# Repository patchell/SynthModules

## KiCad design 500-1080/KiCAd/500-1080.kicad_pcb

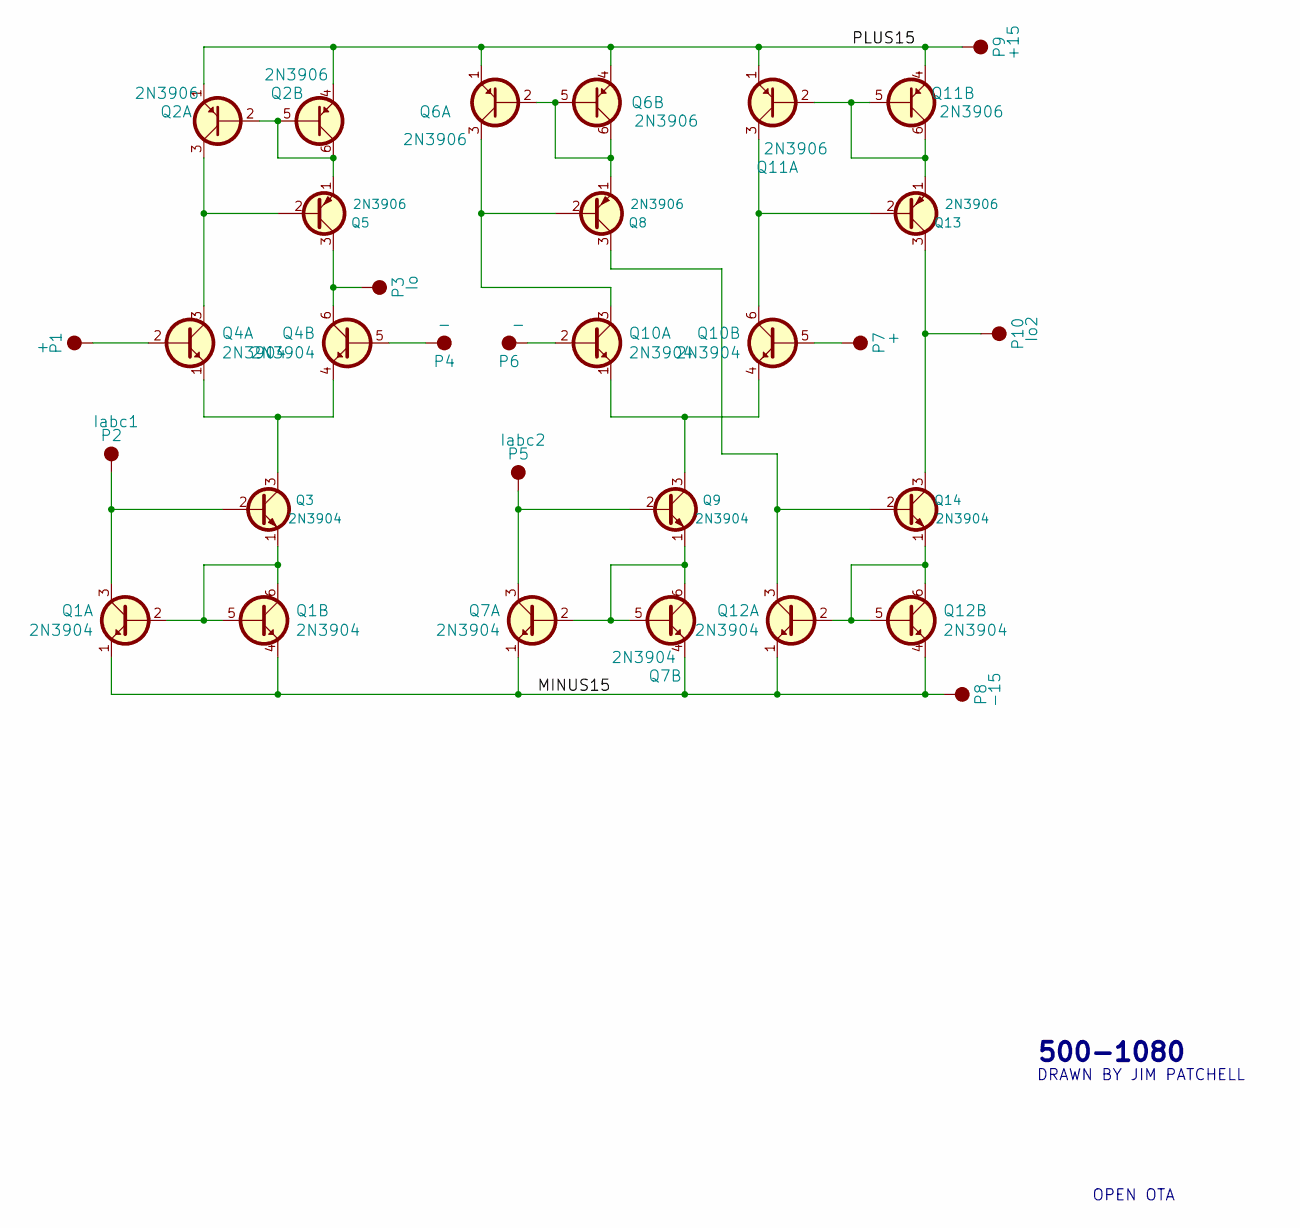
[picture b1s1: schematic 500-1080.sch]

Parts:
P1, P7: +; PAD
P2: Iabc1; PAD
P3: Io; PAD
P4, P6: -; PAD
P5: Iabc2; PAD
P8: -15; PAD
P9: +15; PAD
P10: Io2; PAD
Q1, Q4, Q7, Q10, Q12: 2N3904; DUAL_TO92
Q2, Q6, Q11: 2N3906; DUAL_TO92
Q3, Q9, Q14: 2N3904; TO92
Q5, Q8, Q13: 2N3906; TO92

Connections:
/MINUS15: P8.1, Q1.1 (EMITTER), Q1.4 (EMITTER), Q7.1 (EMITTER), Q7.4 (EMITTER), Q12.1 (EMITTER), Q12.4 (EMITTER)
/PLUS15: P9.1, Q2.1 (Emitter), Q2.4 (Emitter), Q6.1 (Emitter), Q6.4 (Emitter), Q11.1 (Emitter), Q11.4 (Emitter)
unnamed: P1.1, Q4.2 (Base)
unnamed: P2.1, Q1.3 (Collector), Q3.2 (B)
unnamed: P3.1, Q4.6 (Collector), Q5.3 (C)
unnamed: P4.1, Q4.5 (Base)
unnamed: P5.1, Q7.3 (Collector), Q9.2 (B)
unnamed: P6.1, Q10.2 (Base)
unnamed: P7.1, Q10.5 (Base)
unnamed: P10.1, Q13.3 (C), Q14.3 (C)
unnamed: Q1.2 (Base), Q1.5 (Base), Q1.6 (Collector), Q3.1 (E)
unnamed: Q2.2 (Base), Q2.5 (Base), Q2.6 (Collector), Q5.1 (E)
unnamed: Q2.3 (Collector), Q4.3 (Collector), Q5.2 (B)
unnamed: Q3.3 (C), Q4.1 (EMITTER), Q4.4 (EMITTER)
unnamed: Q6.2 (Base), Q6.5 (Base), Q6.6 (Collector), Q8.1 (E)
unnamed: Q7.2 (Base), Q7.5 (Base), Q7.6 (Collector), Q9.1 (E)
unnamed: Q9.3 (C), Q10.1 (EMITTER), Q10.4 (EMITTER)
unnamed: Q6.3 (Collector), Q8.2 (B), Q10.3 (Collector)
unnamed: Q10.6 (Collector), Q11.3 (Collector), Q13.2 (B)
unnamed: Q11.2 (Base), Q11.5 (Base), Q11.6 (Collector), Q13.1 (E)
unnamed: Q12.2 (Base), Q12.5 (Base), Q12.6 (Collector), Q14.1 (E)
unnamed: Q8.3 (C), Q12.3 (Collector), Q14.2 (B)

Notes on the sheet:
OPEN OTA
500-1080
DRAWN BY JIM PATCHELL

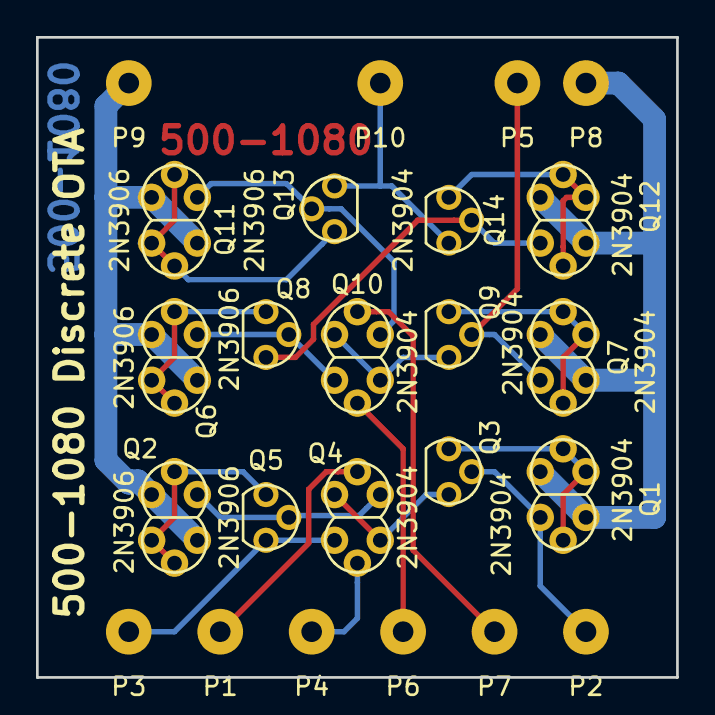
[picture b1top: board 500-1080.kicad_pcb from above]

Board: 2 copper layers, 35.6 x 35.6 mm, 24 parts (0 on the bottom side), 22 nets.

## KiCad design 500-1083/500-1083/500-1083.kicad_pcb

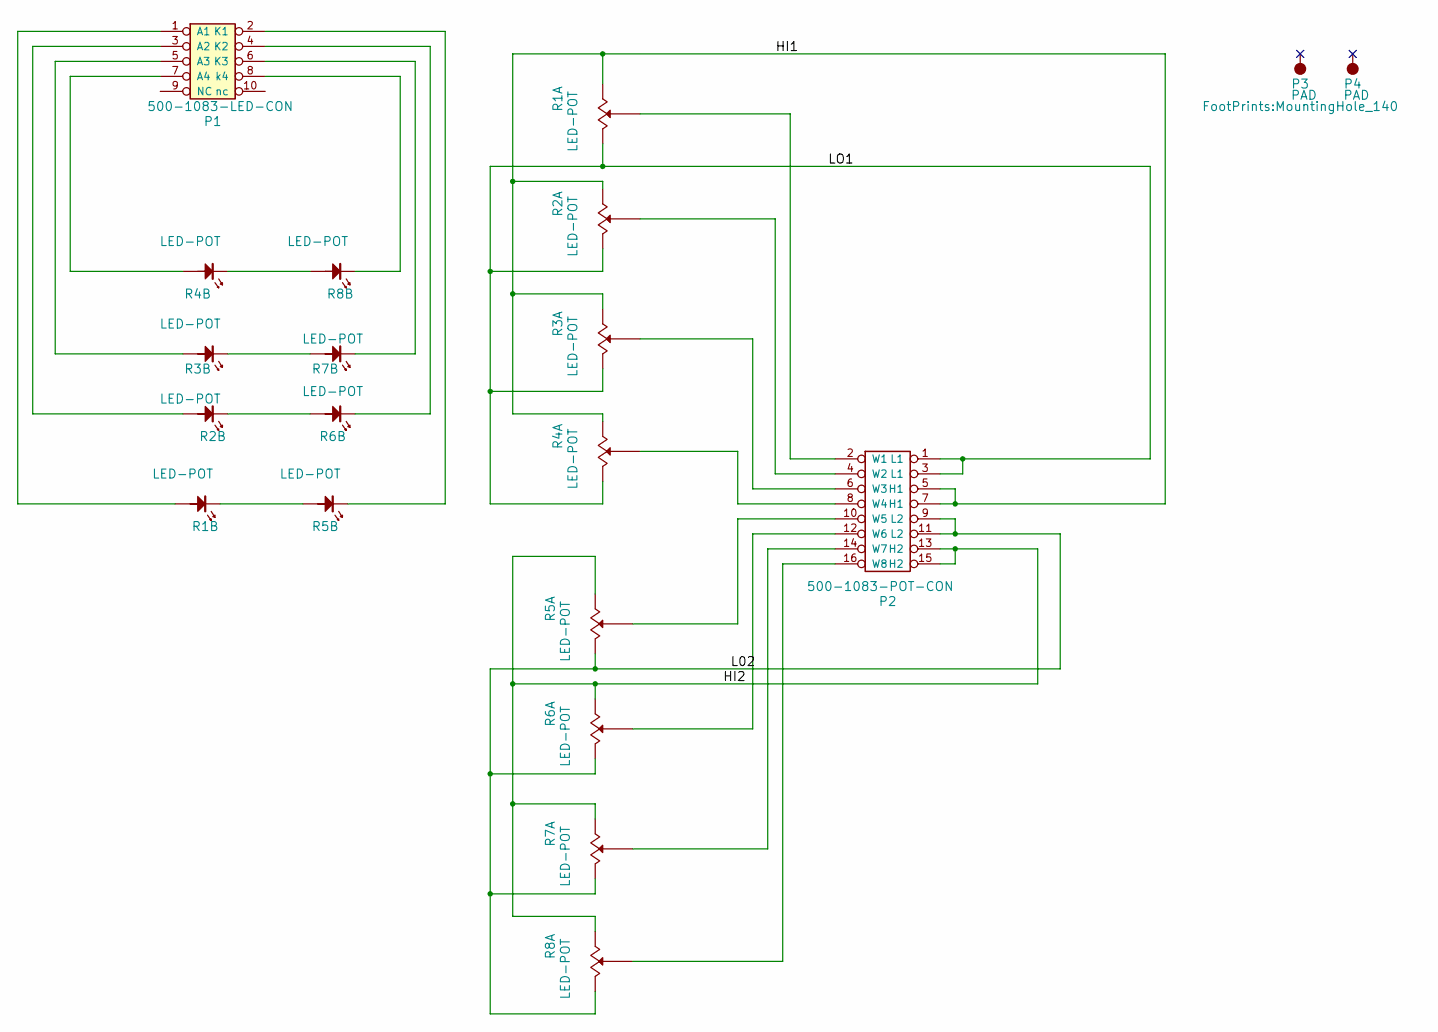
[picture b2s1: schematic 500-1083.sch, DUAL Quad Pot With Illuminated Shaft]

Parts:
P1: 500-1083-LED-CON; IDC5x2_Vert
P2: 500-1083-POT-CON; IDC8x2_Vert
P3, P4: PAD; MountingHole_140
R1, R2, R3, R4, R5, R6, R7, R8: LED-POT; Alpha14mmPotWithLED

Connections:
/HI1: P2.5 (H1), P2.7 (H1), R1.1 (A), R2.1 (A), R3.1 (A), R4.1 (A)
/HI2: P2.13 (H2), P2.15 (H2), R5.1 (A), R6.1 (A), R7.1 (A), R8.1 (A)
/L02: P2.9 (L2), P2.11 (L2), R5.3 (B), R6.3 (B), R7.3 (B), R8.3 (B)
/LO1: P2.1 (L1), P2.3 (L1), R1.3 (B), R2.3 (B), R3.3 (B), R4.3 (B)
unnamed: P1.1 (A1), R1.5 (ANODE)
unnamed: P1.2 (K1), R5.4 (CATHODE)
unnamed: P1.3 (A2), R2.5 (ANODE)
unnamed: P1.4 (K2), R6.4 (CATHODE)
unnamed: P1.5 (A3), R3.5 (ANODE)
unnamed: P1.6 (K3), R7.4 (CATHODE)
unnamed: P1.7 (A4), R4.5 (ANODE)
unnamed: P1.8 (k4), R8.4 (CATHODE)
unnamed: P2.2 (W1), R1.2 (Wiper)
unnamed: P2.4 (W2), R2.2 (Wiper)
unnamed: P2.6 (W3), R3.2 (Wiper)
unnamed: P2.8 (W4), R4.2 (Wiper)
unnamed: P2.10 (W5), R5.2 (Wiper)
unnamed: P2.12 (W6), R6.2 (Wiper)
unnamed: P2.14 (W7), R7.2 (Wiper)
unnamed: P2.16 (W8), R8.2 (Wiper)
unnamed: R1.4 (CATHODE), R5.5 (ANODE)
unnamed: R2.4 (CATHODE), R6.5 (ANODE)
unnamed: R3.4 (CATHODE), R7.5 (ANODE)
unnamed: R4.4 (CATHODE), R8.5 (ANODE)

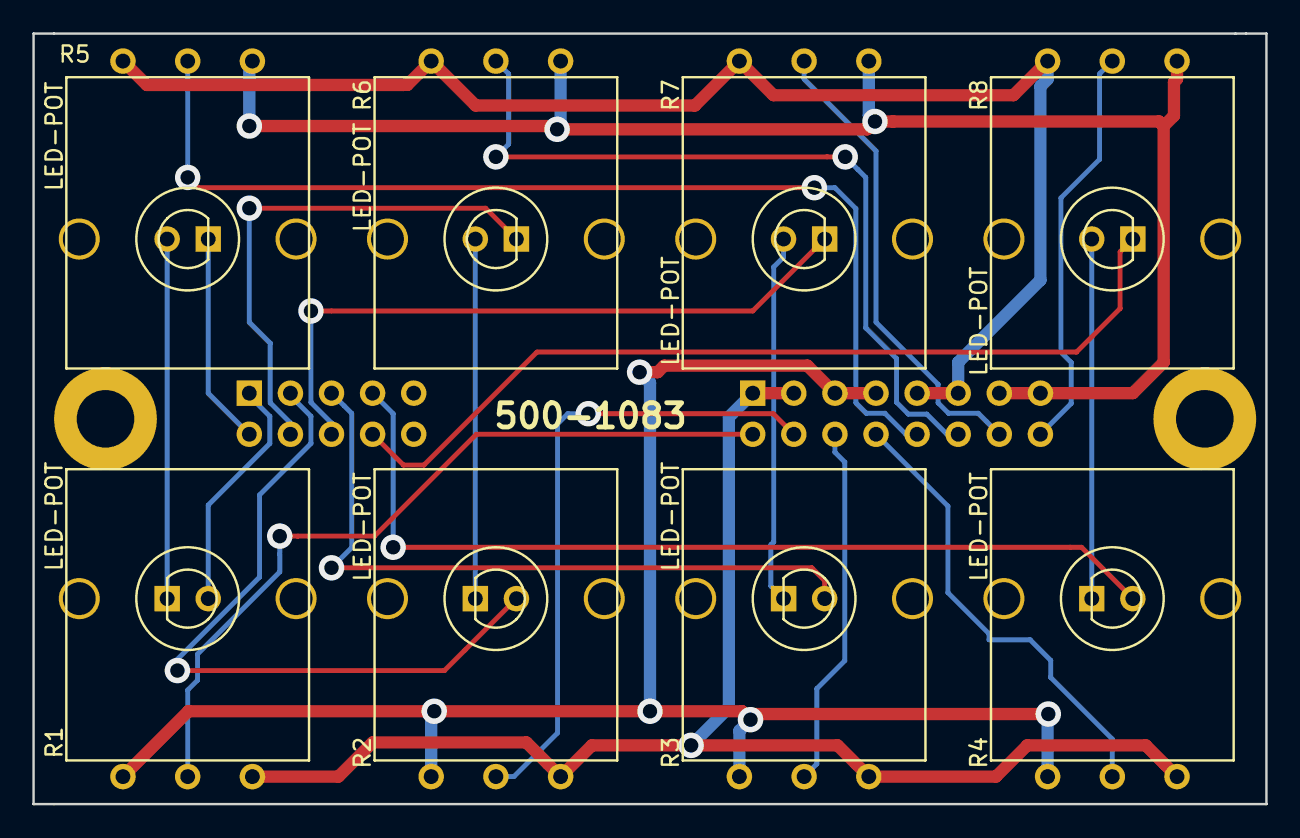
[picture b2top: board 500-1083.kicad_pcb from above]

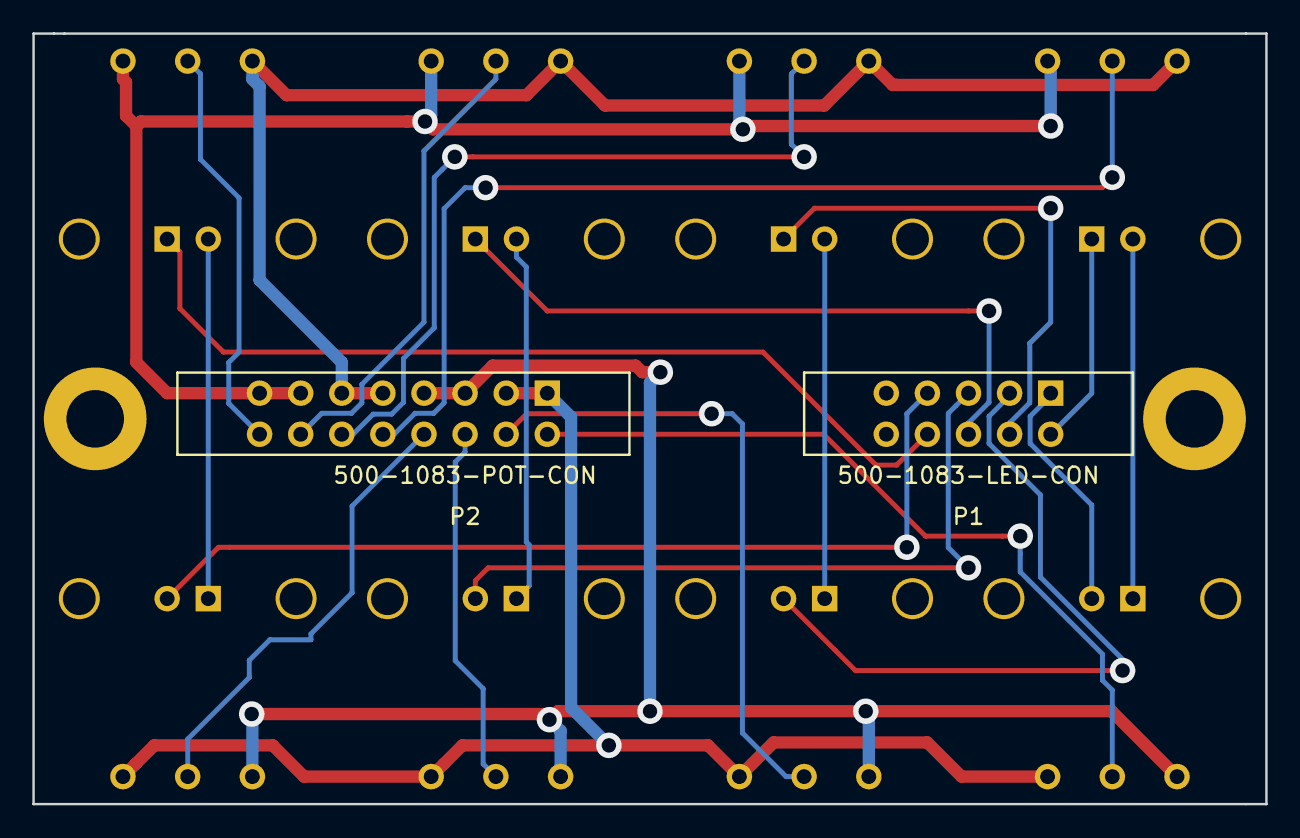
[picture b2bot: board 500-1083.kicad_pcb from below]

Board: 2 copper layers, 76.2 x 47.6 mm, 12 parts (2 on the bottom side), 24 nets.

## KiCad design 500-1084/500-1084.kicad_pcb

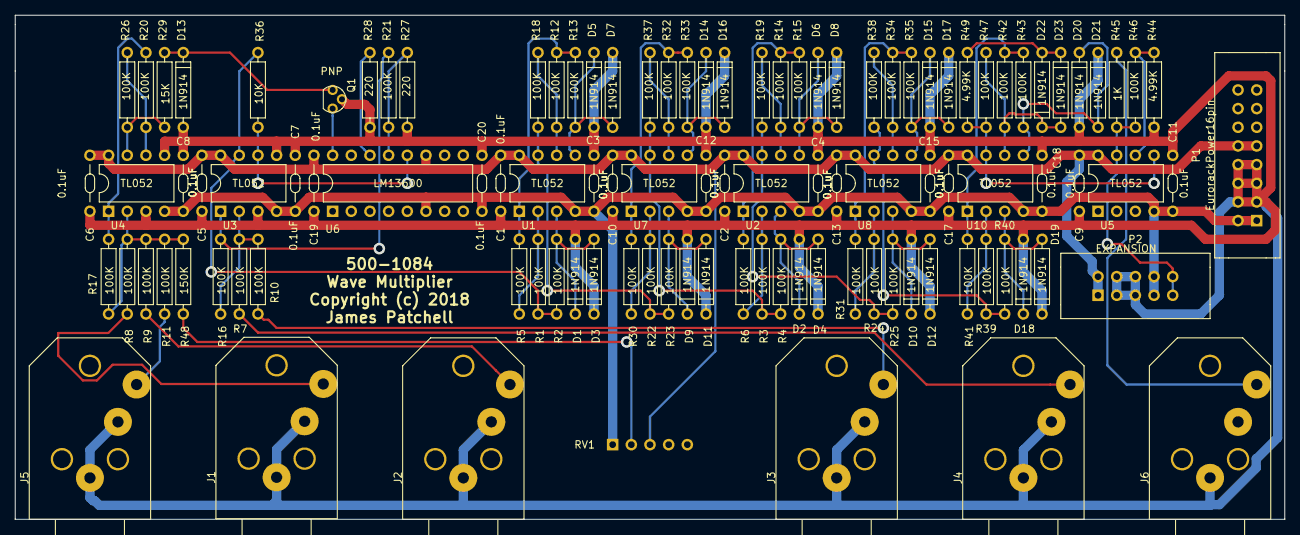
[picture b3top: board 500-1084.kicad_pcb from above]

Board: 2 copper layers, 172.7 x 68.6 mm, 109 parts (0 on the bottom side), 55 nets.

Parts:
C1, C2, C3, C4, C5, C6, C7, C8, C9, C10, C11, C12, C13, C15, C17, C18, C19, C20: 0.1uF; CAP-Bypass-0.3
D1, D2, D3, D4, D5, D6, D7, D8, D9, D10, D11, D12, D13, D14, D15, D16, D17, D18, D19, D20, D21, D22, D23: 1N914; DIODE0.4
J1: FOLDS-2; PHONE-SC112A
J2: FOLDS-3; PHONE-SC112A
J3: INPUT-1; PHONE-SC112A
J4: INPUT-2; PHONE-SC112A
J5: FOLDS-1; PHONE-SC112A
J6: OUT; PHONE-SC112A
P1: EurorackPower16pin; IDC8x2_Vert
P2: EXPANSION; IDC5x2_Vert
Q1: PNP; TO92
R1, R2, R3, R4, R5, R6, R7, R8, R9, R10, R11, R12, R13, R14, R15, R16, R17, R18, R19, R20, R21, R22, R23, R24, R25, R26, R30, R31, R32, R33, R34, R35, R37, R38, R39, R40, R41, R42, R43, R46, R47: 100K; AXIAL0.4
R27, R28: 220; AXIAL0.4
R29: 15K; AXIAL0.4
R36: 10K; AXIAL0.4
R44, R49: 4.99K; AXIAL0.4
R45: 1K; AXIAL0.4
R48: 150K; AXIAL0.4
RV1: FOLDS; 500-1096_RAtoVert
U1, U2, U3, U4, U5, U7, U8, U10: TL052; DIP8.3
U6: LM13600; DIP-16.3

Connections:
+15V0: C1.1, C2.1, C5.1, C6.1, C9.1, C10.1, C13.1, C17.1, C19.1, P1.9, P1.10, P2.1, P2.2, RV1.3, U1.8, U2.8, U3.8, U4.8, U5.8, U6.11, U7.8, U8.8, U10.8
-15V0: C3.1, C4.1, C7.1, C8.1, C11.1, C12.1, C15.1, C18.1, C20.1, P1.1, P1.2, P2.7, P2.8, RV1.1, U1.4, U2.4, U3.4, U4.4, U5.4, U6.6, U7.4, U8.4, U10.4
GND: C1.2, C2.2, C3.2, C4.2, C5.2, C6.2, C7.2, C8.2, C9.2, C10.2, C11.2, C12.2, C13.2, C15.2, C17.2, C18.2, C19.2, C20.2, D1.2, D2.2, D3.1, D4.1, D5.2, D6.2, D7.1, D8.1, D9.2, D10.2, D11.1, D12.1, D13.2, D14.2, D15.2, D16.1, D17.1, D18.2, D19.1, D20.2, D21.1, J1.1, J1.2, J2.1, J2.2, J3.1, J3.2, J4.1, J4.2, J5.1, J5.2, J6.1, P1.3, P1.4, P1.5, P1.6, P1.7, P1.8, P2.3, P2.4, P2.5, P2.6, Q1.2, R27.2, R28.2, R44.2, U3.3, U3.5, U4.3, U4.5
unnamed: D1.1, D3.2, R2.2, U1.3
unnamed: D2.1, D4.2, R4.2, U2.3
unnamed: D5.1, D7.2, R13.2, U1.5
unnamed: D6.1, D8.2, R15.2, U2.5
unnamed: D10.1, D12.2, R25.2, U8.3
unnamed: D9.1, D11.2, R23.2, U7.3
unnamed: D13.1, Q1.1, R29.2
unnamed: D14.1, D16.2, R33.2, U7.5
unnamed: D15.1, D17.2, R35.2, U8.5
unnamed: D18.1, D19.2, R40.2, U10.3
unnamed: D20.1, D21.2, R43.2, U10.5
unnamed: D22.1, D23.2, R42.2, R47.1, U10.6
unnamed: D22.2, D23.1, R49.1
unnamed: J1.3, R8.1
unnamed: J2.3, R9.1
unnamed: J3.3, R10.1
unnamed: J4.3, R7.1
unnamed: J5.3, R11.1
unnamed: J6.3, R45.2
unnamed: P2.9, P2.10, R45.1, R46.2, U5.7
unnamed: Q1.3, U6.16
unnamed: R1.1, R2.1, R36.2, U3.7
unnamed: R1.2, R5.1, U1.2
unnamed: R3.1, R4.1, R37.2, U7.7
unnamed: R3.2, R6.1, U2.2
unnamed: R7.2, R10.2, R16.1, U3.2
unnamed: R8.2, R9.2, R11.2, R17.1, R48.2, U4.2
unnamed: R5.2, R12.1, R13.1, U1.1
unnamed: R12.2, R18.1, U1.6
unnamed: R6.2, R14.1, R15.1, U2.1
unnamed: R14.2, R19.1, U2.6
unnamed: R16.2, R21.1, U3.1
unnamed: R17.2, R20.1, U4.1
unnamed: R18.2, R22.1, R23.1, U1.7
unnamed: R19.2, R24.1, R25.1, U2.7
unnamed: R20.2, R26.1, U4.6
unnamed: R21.2, R27.1, U6.13
unnamed: R22.2, R30.1, U7.2
unnamed: R24.2, R31.1, U8.2
unnamed: R26.2, R29.1, U4.7
unnamed: R28.1, U6.14
unnamed: R30.2, R32.1, R33.1, U7.1
unnamed: R31.2, R34.1, R35.1, U8.1
unnamed: R32.2, R37.1, U7.6
unnamed: R34.2, R38.1, U8.6
unnamed: R36.1, U3.6, U6.12
unnamed: R38.2, R39.1, R40.1, U8.7
unnamed: R39.2, R41.1, U10.2
unnamed: R41.2, R42.1, R43.1, U10.1
unnamed: R44.1, R46.1, U5.6
unnamed: R47.2, R49.2, U5.5, U10.7
unnamed: R48.1, RV1.2

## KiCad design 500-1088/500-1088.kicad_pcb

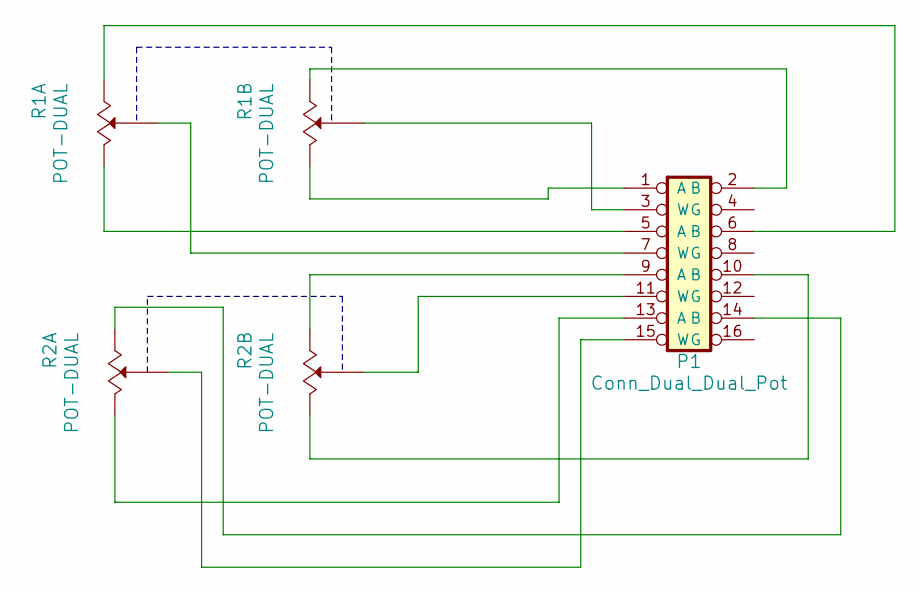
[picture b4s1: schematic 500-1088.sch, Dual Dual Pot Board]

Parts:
P1: Conn_Dual_Dual_Pot; IDC8x2_Vert
R1, R2: POT-DUAL; AlphaRD902DualPot

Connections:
unnamed: P1.1 (A), R1.5 (B)
unnamed: P1.2 (B), R1.4 (A)
unnamed: P1.3 (W), R1.6 (Wiper)
unnamed: P1.5 (A), R1.2 (B)
unnamed: P1.6 (B), R1.1 (A)
unnamed: P1.7 (W), R1.3 (Wiper)
unnamed: P1.9 (A), R2.4 (A)
unnamed: P1.10 (B), R2.5 (B)
unnamed: P1.11 (W), R2.6 (Wiper)
unnamed: P1.13 (A), R2.2 (B)
unnamed: P1.14 (B), R2.1 (A)
unnamed: P1.15 (W), R2.3 (Wiper)

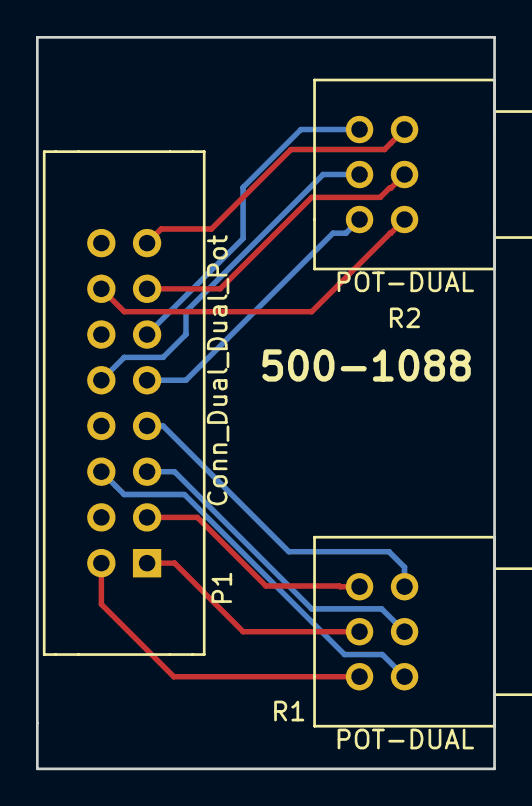
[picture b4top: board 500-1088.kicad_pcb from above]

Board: 2 copper layers, 25.4 x 40.6 mm, 3 parts (0 on the bottom side), 12 nets.

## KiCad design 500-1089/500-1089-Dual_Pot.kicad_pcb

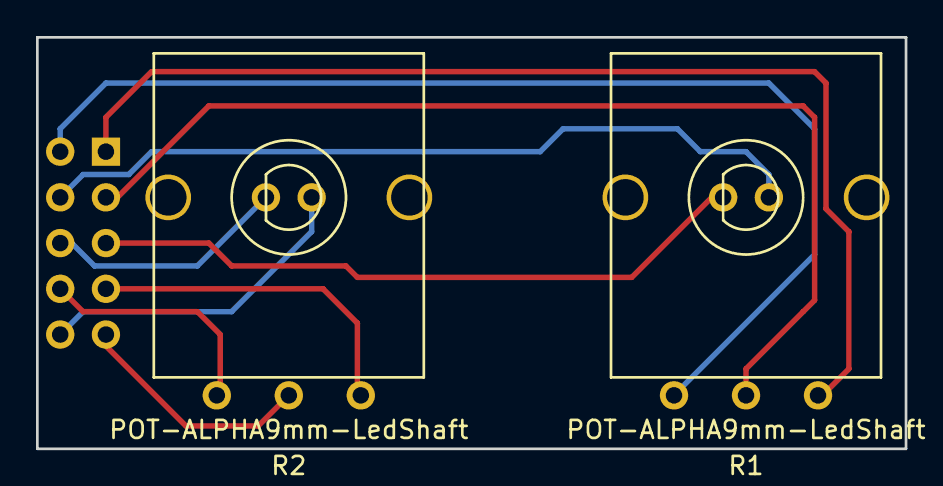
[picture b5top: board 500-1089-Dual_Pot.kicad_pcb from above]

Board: 2 copper layers, 48.3 x 22.9 mm, 3 parts (0 on the bottom side), 10 nets.

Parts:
P1: CONN_02X05; IDC5x2rear
R1, R2: POT-ALPHA9mm-LedShaft; Alpha14mmPotWithLED

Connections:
unnamed: P1.1, R1.3
unnamed: P1.2, R1.1
unnamed: P1.3, R1.2
unnamed: P1.4, R1.5
unnamed: P1.5, R1.4
unnamed: P1.6, R2.4
unnamed: P1.7, R2.3
unnamed: P1.8, R2.1
unnamed: P1.9, R2.2
unnamed: P1.10, R2.5

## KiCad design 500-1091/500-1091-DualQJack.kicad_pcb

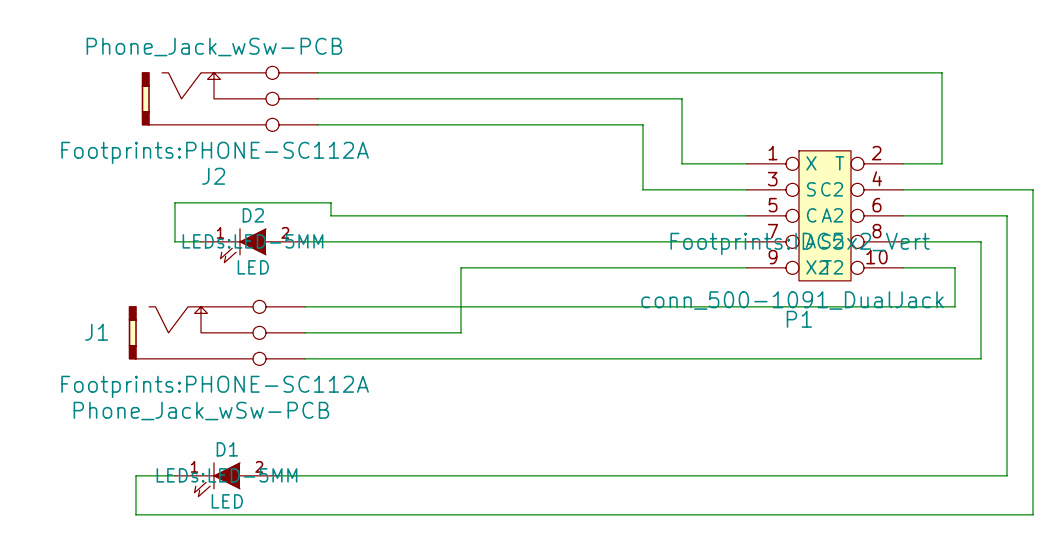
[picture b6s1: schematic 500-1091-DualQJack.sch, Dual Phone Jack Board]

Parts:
D1, D2: LED; LED-5MM
J1, J2: Phone_Jack_wSw-PCB; PHONE-SC112A
P1: conn_500-1091_DualJack; IDC5x2_Vert

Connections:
unnamed: D1.1 (K), P1.4 (C2)
unnamed: D1.2 (A), P1.6 (A2)
unnamed: D2.1 (K), P1.5 (C)
unnamed: D2.2 (A), P1.7 (A)
unnamed: J1.1 (Gnd), P1.8 (S2)
unnamed: J1.2 (Sw), P1.9 (X2)
unnamed: J1.3 (Tip), P1.10 (T2)
unnamed: J2.1 (Gnd), P1.3 (S)
unnamed: J2.2 (Sw), P1.1 (X)
unnamed: J2.3 (Tip), P1.2 (T)

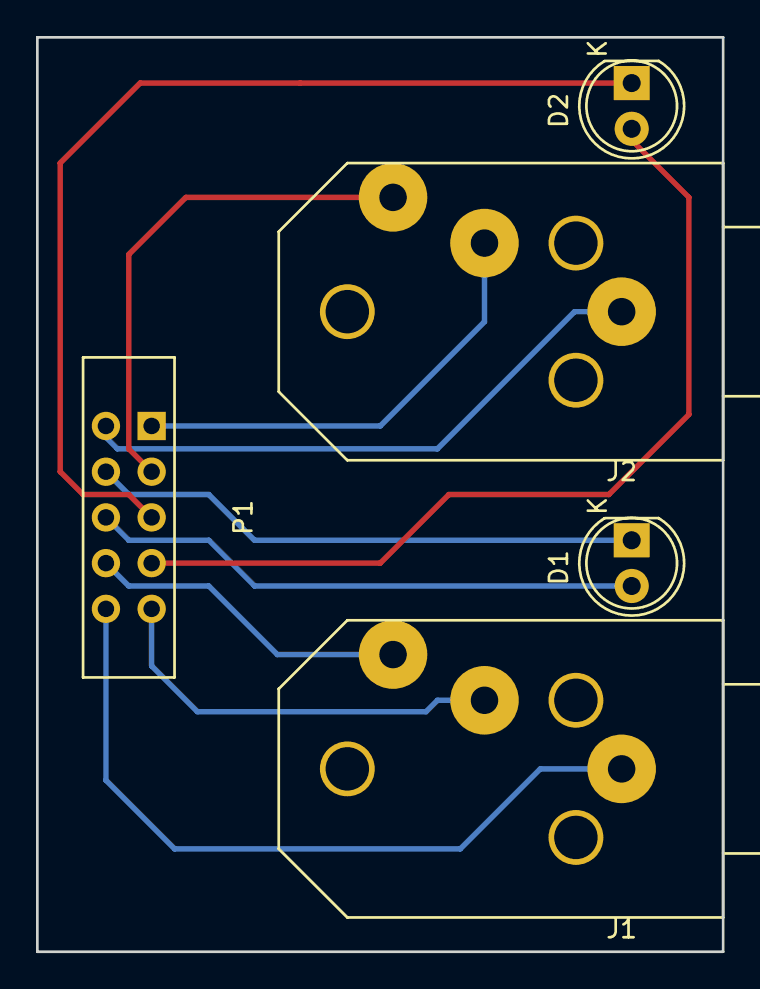
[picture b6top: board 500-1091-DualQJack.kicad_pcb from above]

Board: 2 copper layers, 38.1 x 50.8 mm, 5 parts (0 on the bottom side), 10 nets.

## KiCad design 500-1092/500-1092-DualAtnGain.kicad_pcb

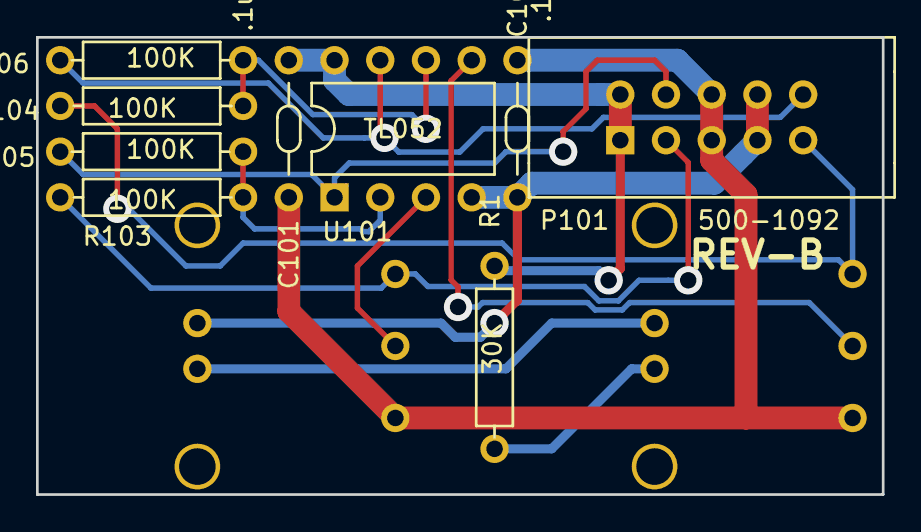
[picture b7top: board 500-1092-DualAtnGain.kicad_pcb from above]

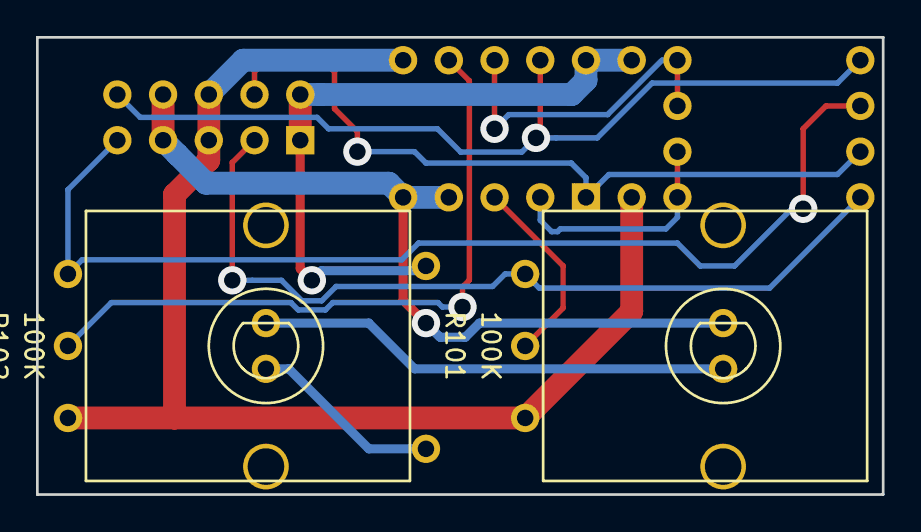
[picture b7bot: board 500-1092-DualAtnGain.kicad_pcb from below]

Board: 2 copper layers, 47.0 x 25.4 mm, 11 parts (2 on the bottom side), 13 nets.

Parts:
C101, C102: .1uF; CAP-Bypass-0.3
P101: 500-1092; IDC5x2_Vert
R1: 30K; AXIAL0_4
R101, R102: 100K; Alpha9mmPotWithLED
R103, R104, R105, R106: 100K; AXIAL0.4
U101: TL052; DIP8.3

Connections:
/V+: C101.1, P101.1, P101.2, R1.1, U101.8
/V-: C102.1, P101.7, P101.8, R101.4, U101.4
GND: C101.2, C102.2, P101.5, P101.6, R101.3, R102.3
unnamed: P101.3, R101.1, R103.1
unnamed: P101.4, R105.2, U101.1
unnamed: P101.9, R102.1, R104.1
unnamed: P101.10, R106.2, U101.7
unnamed: R1.2, R102.5
unnamed: R101.2, U101.3
unnamed: R101.5, R102.4
unnamed: R102.2, U101.5
unnamed: R103.2, R105.1, U101.2
unnamed: R104.2, R106.1, U101.6

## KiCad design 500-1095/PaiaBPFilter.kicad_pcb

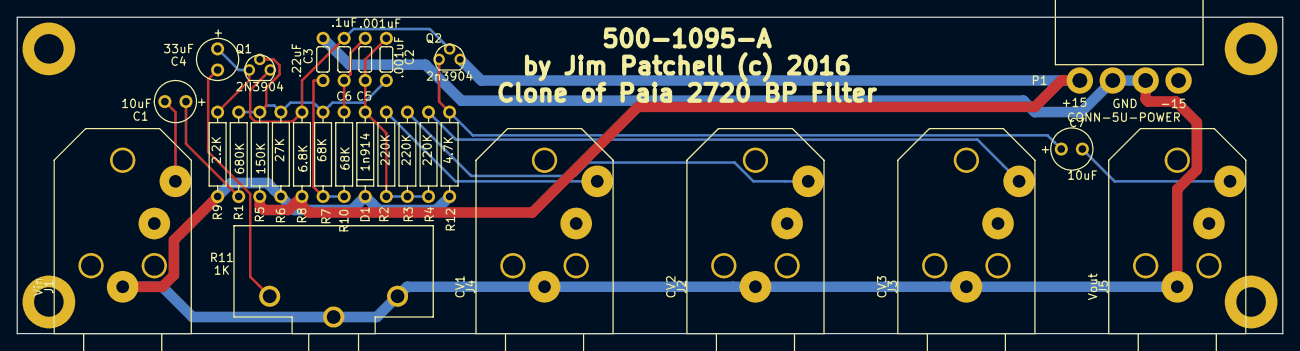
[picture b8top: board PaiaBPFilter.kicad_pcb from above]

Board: 2 copper layers, 152.4 x 38.1 mm, 28 parts (0 on the bottom side), 16 nets.

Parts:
C1, C7: 10uF; CapPol-Rad-0.2x0.1
C2, C5: .001uF; CAP-GREENIE-0.2
C3: .22uF; CAP-GREENIE-0.2
C4: 33uF; CapPol-Rad-0.2x0.1
C6: .1uF; CAP-GREENIE-0.2
D1: 1n914; DIODE0.4
J1: Vin; PHONE-SC112A
J2: CV2; PHONE-SC112A
J3: CV3; PHONE-SC112A
J4: CV1; PHONE-SC112A
J5: Vout; PHONE-SC112A
P1: CONN-5U-POWER; CONN-5U-POWER-RA
Q1: 2N3904; TO92
Q2: 2n3904; TO92
R1: 680K; AXIAL0.4
R2, R3, R4: 220K; AXIAL0.4
R5: 150K; AXIAL0.4
R6: 27K; AXIAL0.4
R7, R10: 68K; AXIAL0.4
R8: 6.8K; AXIAL0.4
R9: 2.2K; AXIAL0.4
R11: 1K; POT-Alpha-24mm-RA
R12: 4.7K; AXIAL0.4

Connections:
/+15: P1.1, Q2.3, R5.1, R8.1
GND: C3.2, D1.1, J1.1, J2.1, J3.1, J4.1, J5.1, P1.2, P1.3, R6.2, R9.2, R11.2, R11.3, R12.2
unnamed: C1.1, R1.1
unnamed: C1.2, J1.3
unnamed: C2.1, Q1.2, R1.2, R5.2, R6.1, R7.1
unnamed: C2.2, C5.1, D1.2, R2.2, R3.2, R4.2
unnamed: C3.1, R7.2, R10.1
unnamed: C4.1, Q1.1, R9.1
unnamed: C4.2, R11.1
unnamed: C5.2, C6.1, R10.2
unnamed: C6.2, Q1.3, Q2.2, R8.2
unnamed: C7.1, Q2.1, R12.1
unnamed: C7.2, J5.3
unnamed: J2.3, R3.1
unnamed: J3.3, R4.1
unnamed: J4.3, R2.1

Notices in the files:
500-1084/500-1084.kicad_pcb:
Copyright (c) 2018
500-1095/PaiaBPFilter.kicad_pcb:
by Jim Patchell (c) 2016
